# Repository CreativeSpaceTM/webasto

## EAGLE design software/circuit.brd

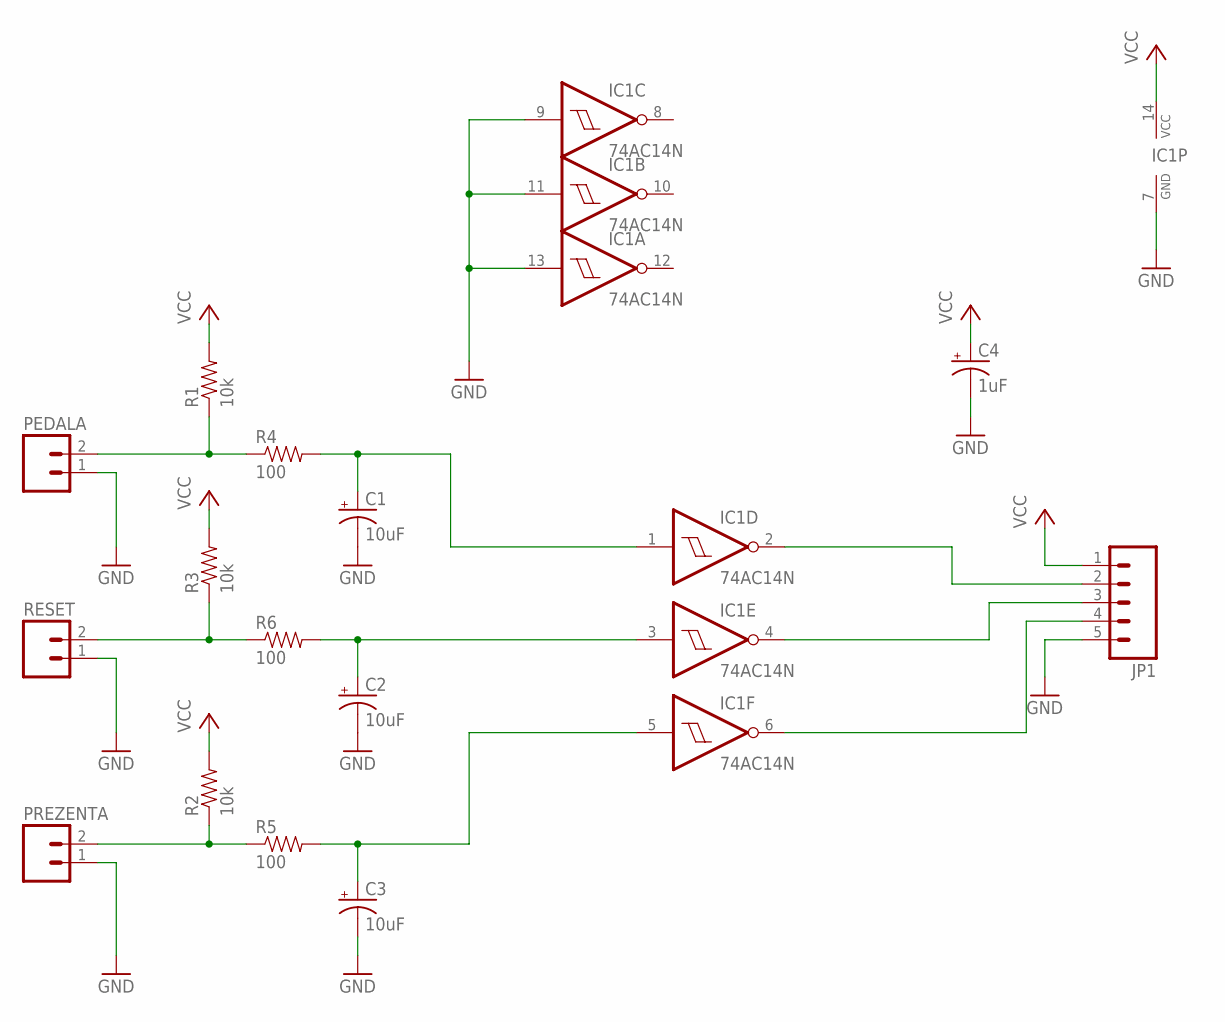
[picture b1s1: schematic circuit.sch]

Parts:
C1, C2, C3: 10uF; CPOL-RADIAL-10UF-25V
C4: 1uF; CPOL-RADIAL-10UF-25V
IC1: 74AC14N; DIL14
JP1: M05PTH_LONGPADS; 1X05_LONGPADS
PEDALA: M025MM; SCREWTERMINAL-5MM-2
PREZENTA: M025MM; SCREWTERMINAL-5MM-2
R1, R2, R3: 10k; AXIAL-0.4
R4, R5, R6: 100; AXIAL-0.4
RESET: M025MM; SCREWTERMINAL-5MM-2

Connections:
GND: C1.2 (-), C2.2 (-), C3.2 (-), C4.2 (-), IC1.7 (GND), IC1.9 (I), IC1.11 (I), IC1.13 (I), JP1.5, PEDALA.1, PREZENTA.1, RESET.1
unnamed: PEDALA.2, R1.P$1 (1), R4.P$1 (1)
unnamed: C1.1 (+), IC1.1 (I), R4.P$2 (2)
unnamed: R3.P$1 (1), R6.P$1 (1), RESET.2
unnamed: C2.1 (+), IC1.3 (I), R6.P$2 (2)
unnamed: PREZENTA.2, R2.P$1 (1), R5.P$1 (1)
unnamed: C3.1 (+), IC1.5 (I), R5.P$2 (2)
unnamed: IC1.2 (O), JP1.2
unnamed: IC1.4 (O), JP1.3
unnamed: IC1.6 (O), JP1.4
VCC: C4.1 (+), IC1.14 (VCC), JP1.1, R1.P$2 (2), R2.P$2 (2), R3.P$2 (2)

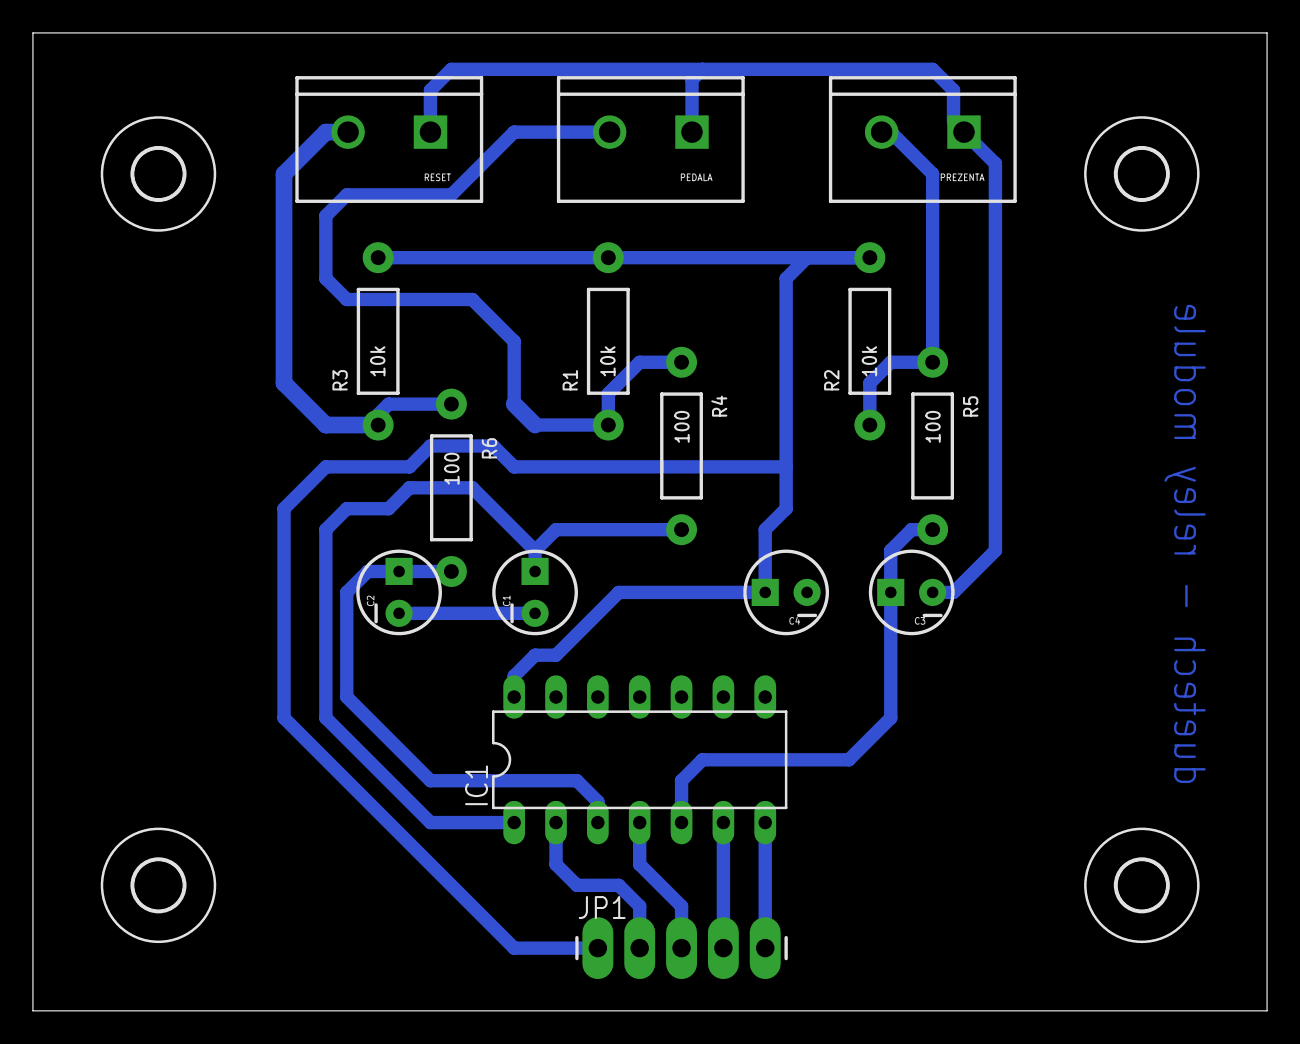
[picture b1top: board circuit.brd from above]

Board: 2 copper layers, 74.9 x 59.4 mm, 19 parts (0 on the bottom side), 11 nets.

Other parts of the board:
U$1, U$2, U$3, U$4: 3,0

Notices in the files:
parts and their libraries:
SparkFun-Connectors: Licensing: CC v3.0 Share-Alike You are welcome to use this library for commercial purposes.
